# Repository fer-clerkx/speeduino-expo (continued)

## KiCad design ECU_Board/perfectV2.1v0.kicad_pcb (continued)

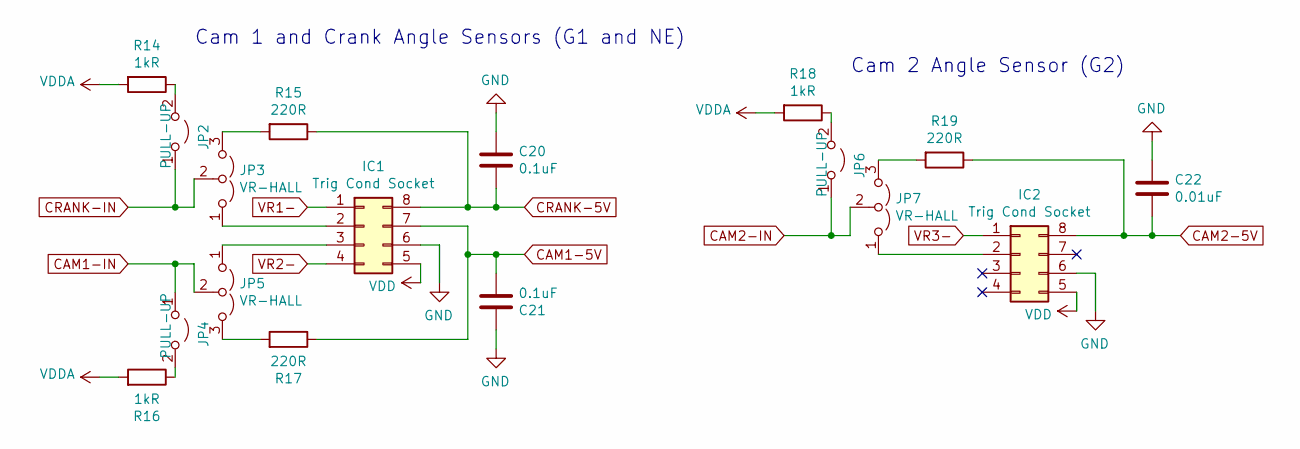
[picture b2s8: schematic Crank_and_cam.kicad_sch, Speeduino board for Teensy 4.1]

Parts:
C20, C21: 0.1uF; C_0805_2012Metric; Manufacturer_Part_Number VJ0805Y104KXAPW1BC; Digikey Part Number 3296136
C22: 0.01uF; C_0805_2012Metric; Manufacturer_Part_Number CC0805KRX7R9BB103; Digikey Part Number 3019937
IC1, IC2: Trig Cond Socket; DIP-8_W7.62mm_Socket; Manufacturer_Part_Number 2227MC-08-03-18-F1; Digikey Part Number 1103844
JP2, JP4, JP6: PULL-UP; PinHeader_1x02_P2.54mm_Vertical
JP3, JP5, JP7: VR-HALL; PinHeader_1x03_P2.54mm_Vertical
R14, R16, R18: 1kR; R_0402_1005Metric; Manufacturer_Part_Number WF04P1001FTL; Digikey Part Number 2502798
R15, R17, R19: 220R; R_0603_1608Metric; Manufacturer_Part_Number MR06X2200FTLV; Digikey Part Number 3994459

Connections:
CAM1-5V: C21.2, IC1.7, R17.1; also elsewhere on the board
CAM1-IN: JP4.1 (A), JP5.2 (C); also elsewhere on the board
CAM2-5V: C22.2, IC2.8, R19.1; also elsewhere on the board
CAM2-IN: JP6.1 (A), JP7.2 (C); also elsewhere on the board
CRANK-5V: C20.2, IC1.8, R15.1; also elsewhere on the board
CRANK-IN: JP2.1 (A), JP3.2 (C); also elsewhere on the board
GND: C20.1, C21.1, C22.1, IC1.6, IC2.6; also elsewhere on the board
unnamed: IC1.2, JP3.1 (A)
unnamed: IC1.3, JP5.1 (A)
unnamed: IC2.2, JP7.1 (A)
unnamed: JP2.2 (B), R14.1
unnamed: JP3.3 (B), R15.2
unnamed: JP4.2 (B), R16.1
unnamed: JP5.3 (B), R17.2
unnamed: JP6.2 (B), R18.1
unnamed: JP7.3 (B), R19.2
VDD: IC1.5, IC2.5; also elsewhere on the board
VDDA: R14.2, R16.2, R18.2; also elsewhere on the board
VR1-: IC1.1; also elsewhere on the board
VR2-: IC1.4; also elsewhere on the board
VR3-: IC2.1; also elsewhere on the board

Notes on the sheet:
Cam 1 and Crank Angle Sensors (G1 and NE)
Cam 2 Angle Sensor (G2)

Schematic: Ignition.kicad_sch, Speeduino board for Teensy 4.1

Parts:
C23, C25: 0.1uF; C_0805_2012Metric; Manufacturer_Part_Number VJ0805Y104KXAPW1BC; Digikey Part Number 3296136
C24, C26: 1uF; C_0805_2012Metric; Manufacturer_Part_Number CC0805KKX7R7BB105; Digikey Part Number 3369302
D13, D14, D15, D16: LED; LED_0805_2012Metric; Manufacturer_Part_Number MP008293; Digikey Part Number 3796325
JP8: Ignition Voltage; PinHeader_1x03_P2.54mm_Vertical
R32, R35, R40, R43: 100kR; R_0402_1005Metric; Manufacturer_Part_Number WF04P1003FTL; Digikey Part Number 2502803
R33, R34, R41, R42: 1kR; R_0402_1005Metric; Manufacturer_Part_Number WF04P1001FTL; Digikey Part Number 2502798
R36, R39, R44, R47: 2k4R; R_0805_2012Metric; Manufacturer_Part_Number MCWR08X2401FTL; Digikey Part Number 2447625
R37, R38, R45, R46: 10R; R_0402_1005Metric; Manufacturer_Part_Number WF04P10R0FTL; Digikey Part Number 2502794
U6, U7: TC4424A; SOIC-8_3.9x4.9mm_P1.27mm; Manufacturer_Part_Number TC4424AVOA; Digikey Part Number 738-6067

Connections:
+12V: JP8.3 (B); also elsewhere on the board
GND: C23.1, C24.1, C25.1, C26.1, D13.1 (K), D14.1 (K), D15.1 (K), D16.1 (K), R32.2, R35.1, R40.2, R43.1, U6.3 (GND), U7.3 (GND); also elsewhere on the board
IGN-1-OUT: R38.1; also elsewhere on the board
IGN-2-OUT: R37.1; also elsewhere on the board
IGN-3-OUT: R46.1; also elsewhere on the board
IGN-4-OUT: R45.1; also elsewhere on the board
MCU-IGN1: R34.2, R35.2; also elsewhere on the board
MCU-IGN2: R32.1, R33.2; also elsewhere on the board
MCU-IGN3: R42.2, R43.2; also elsewhere on the board
MCU-IGN4: R40.1, R41.2; also elsewhere on the board
unnamed: D13.2 (A), R36.2
unnamed: D14.2 (A), R39.2
unnamed: D15.2 (A), R44.2
unnamed: D16.2 (A), R47.2
unnamed: R33.1, U6.2 (IN_A)
unnamed: R34.1, U6.4 (IN_B)
unnamed: R36.1, R37.2, U6.7 (OUT_A)
unnamed: R38.2, R39.1, U6.5 (OUT_B)
unnamed: R41.1, U7.2 (IN_A)
unnamed: R42.1, U7.4 (IN_B)
unnamed: R44.1, R45.2, U7.7 (OUT_A)
unnamed: R46.2, R47.1, U7.5 (OUT_B)
VDD: JP8.1 (A); also elsewhere on the board
Vdrive: C23.2, C24.2, C25.2, C26.2, JP8.2 (C), U6.6 (VDD), U7.6 (VDD)

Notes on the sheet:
Ignition Driver 2
Ignition Driver 1

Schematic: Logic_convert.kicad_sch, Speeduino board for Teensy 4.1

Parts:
C30, C31, C32, C33, C34, C35, C36, C37: 0.1uF; C_0805_2012Metric; Manufacturer_Part_Number VJ0805Y104KXAPW1BC; Digikey Part Number 3296136
R60, R62, R64, R66, R68, R70: 180kR +/-0.1%; R_0805_2012Metric; Manufacturer_Part_Number MCWF08R1803BTL; Digikey Part Number 2337663
R61, R63, R65, R67, R69, R71: 330kR +/-0.1%; R_0805_2012Metric; Manufacturer_Part_Number MCWF08R3303BTL; Digikey Part Number 2337789
U10, U11: LM324A; SOIC-14_3.9x8.7mm_P1.27mm; Manufacturer_Part_Number LM324ADR; Digikey Part Number 3117046
U12, U13, U14: CD4504B; TSSOP-16_4.4x5mm_P0.65mm; Manufacturer_Part_Number CD4504BPW; Digikey Part Number 3006769

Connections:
+3V3: C30.1, C31.1, C33.1, C34.1, C36.1, U10.4 (V+), U11.4 (V+), U12.16 (VDD), U13.1 (VCC), U14.1 (VCC); also elsewhere on the board
ACIS-5V: U14.2 (Aout); also elsewhere on the board
BAT-5V: R68.2; also elsewhere on the board
CAM1-5V: U12.9 (Din); also elsewhere on the board
CAM2-5V: U12.11 (Ein); also elsewhere on the board
CLT-5V: R70.2; also elsewhere on the board
CRANK-5V: U12.7 (Cin); also elsewhere on the board
FLEX-IN: U12.3 (Ain); also elsewhere on the board
GND: C30.2, C31.2, C32.2, C33.2, C34.2, C35.2, C36.2, C37.2, R61.1, R63.1, R65.1, R67.1, R69.1, R71.1, U10.11 (V-), U11.11 (V-), U12.5 (Bin), U12.8 (VSS), U12.13 (Select), U12.14 (Fin), U13.8 (VSS), U13.13 (Select), U13.14 (Fin), U14.8 (VSS), U14.9 (Din), U14.11 (Ein), U14.13 (Select), U14.14 (Fin); also elsewhere on the board
HC1-5V: U13.6 (Cout); also elsewhere on the board
HC2-5V: U13.2 (Aout); also elsewhere on the board
IAT-5V: R66.2; also elsewhere on the board
IDLE-5V: U13.4 (Bout); also elsewhere on the board
INJ1-5V: U14.4 (Bout); also elsewhere on the board
INJ2-5V: U14.6 (Cout); also elsewhere on the board
INJ3-5V: U13.12 (Eout); also elsewhere on the board
INJ4-5V: U13.10 (Dout); also elsewhere on the board
MAP-5V: R60.2; also elsewhere on the board
MCU-ACIS: U14.3 (Ain); also elsewhere on the board
MCU-BAT: U11.1, U11.2 (-); also elsewhere on the board
MCU-CAM1: U12.10 (Dout); also elsewhere on the board
MCU-CAM2: U12.12 (Eout); also elsewhere on the board
MCU-CLT: U11.6 (-), U11.7; also elsewhere on the board
MCU-CRANK: U12.6 (Cout); also elsewhere on the board
MCU-FLEX: U12.2 (Aout); also elsewhere on the board
MCU-HC1: U13.7 (Cin); also elsewhere on the board
MCU-HC2: U13.3 (Ain); also elsewhere on the board
MCU-IAT: U10.13 (-), U10.14; also elsewhere on the board
MCU-IDLE: U13.5 (Bin); also elsewhere on the board
MCU-INJ1: U14.5 (Bin); also elsewhere on the board
MCU-INJ2: U14.7 (Cin); also elsewhere on the board
MCU-INJ3: U13.11 (Ein); also elsewhere on the board
MCU-INJ4: U13.9 (Din); also elsewhere on the board
MCU-MAP: U10.1, U10.2 (-); also elsewhere on the board
MCU-O2: U10.8, U10.9 (-); also elsewhere on the board
MCU-TPS: U10.6 (-), U10.7; also elsewhere on the board
unnamed: R60.1, R61.2, U10.3 (+)
unnamed: R62.1, R63.2, U10.5 (+)
unnamed: R64.1, R65.2, U10.10 (+)
unnamed: R66.1, R67.2, U10.12 (+)
unnamed: R68.1, R69.2, U11.3 (+)
unnamed: R70.1, R71.2, U11.5 (+)
O2-5V: R64.2; also elsewhere on the board
TPS-5V: R62.2; also elsewhere on the board
VDD: C32.1, C35.1, C37.1, U12.1 (VCC), U13.16 (VDD), U14.16 (VDD); also elsewhere on the board

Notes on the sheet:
Digital outputs
Digital inputs
Inlet air temperature sensor
MAP sensor
Battery refrence voltage
Coolant temperature sensor
Throttle position sensor
O2 sensor

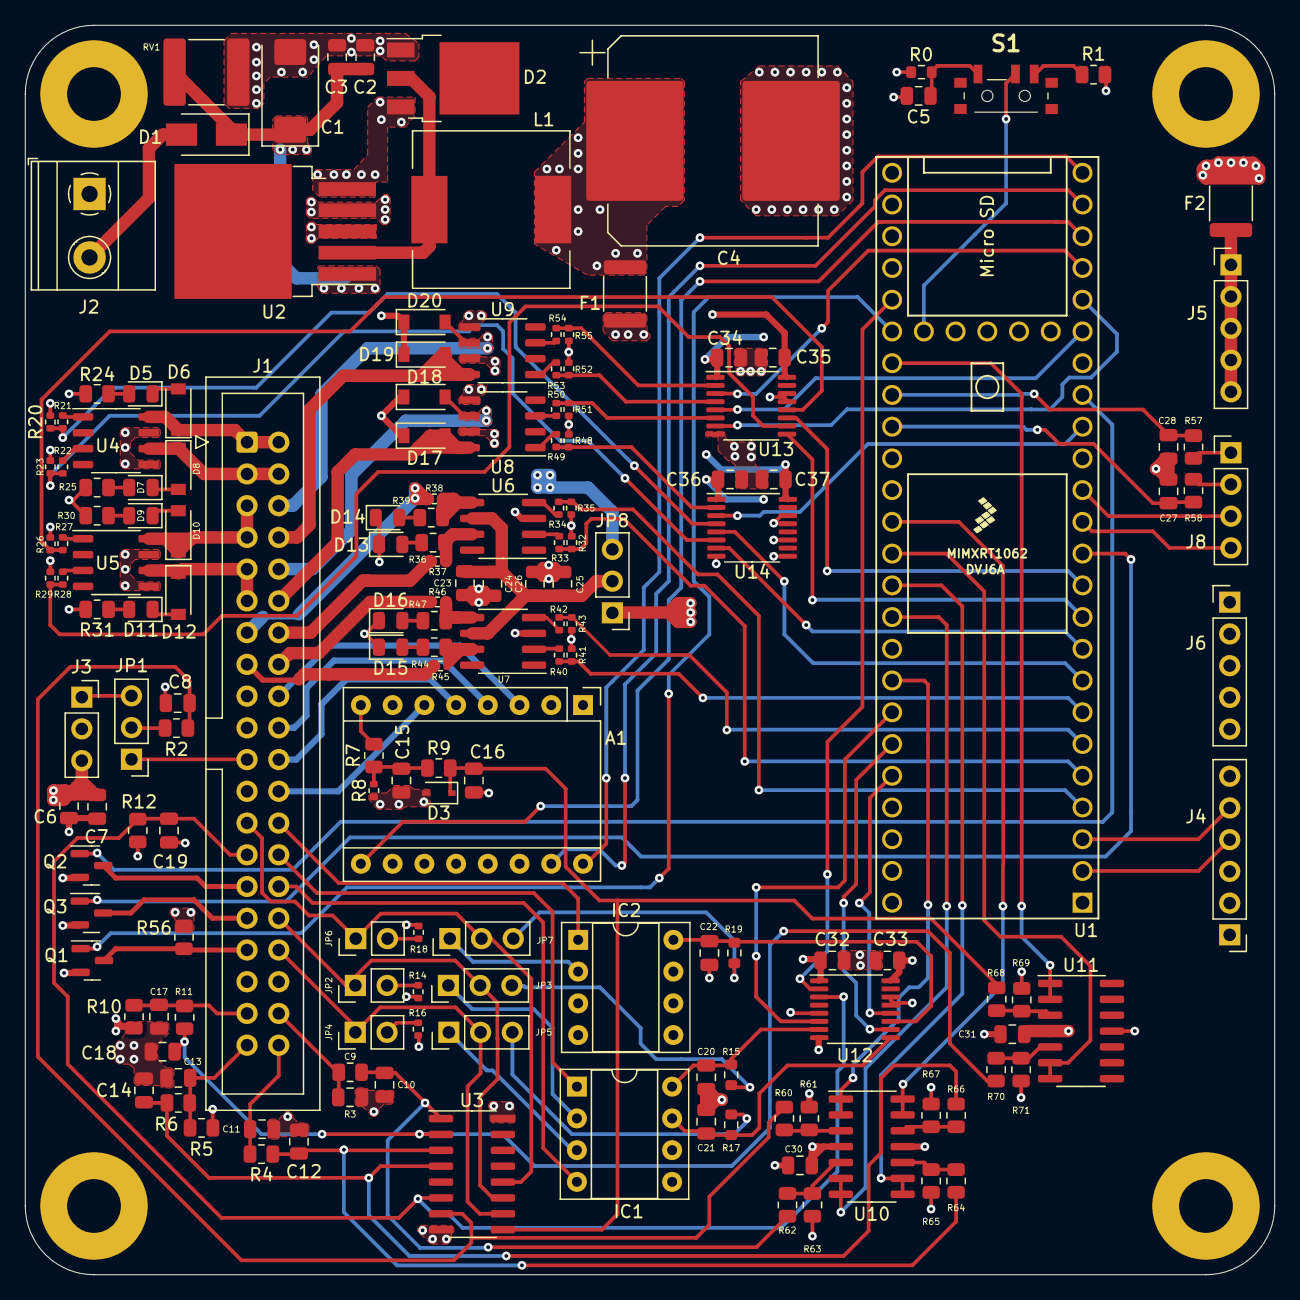
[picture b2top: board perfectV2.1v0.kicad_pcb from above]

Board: 4 copper layers, 100.0 x 100.0 mm, 169 parts (0 on the bottom side), 142 nets.

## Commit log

2023-01-04 Removed previous PCB layout, updated title blocks, changed stackup
2023-01-04 Assigned fp to mounting holes, removed datasheet fields
2023-01-04 Swapped which angle sensors are connected to VR conditioners
2023-01-06 Completed layout, slight changes to schematic to optimise routing, 12V proto supply rail removed
2023-01-06 Added adapter board
2023-01-07 Removed clutch input
2023-01-07 Updated gerber files
2023-01-07 Changed Boost output to ACIS
2023-01-07 Finished adapter board, slight changes to ECU
2023-01-08 Added dril files
2023-01-09 Fixed silkscreen mirroring
